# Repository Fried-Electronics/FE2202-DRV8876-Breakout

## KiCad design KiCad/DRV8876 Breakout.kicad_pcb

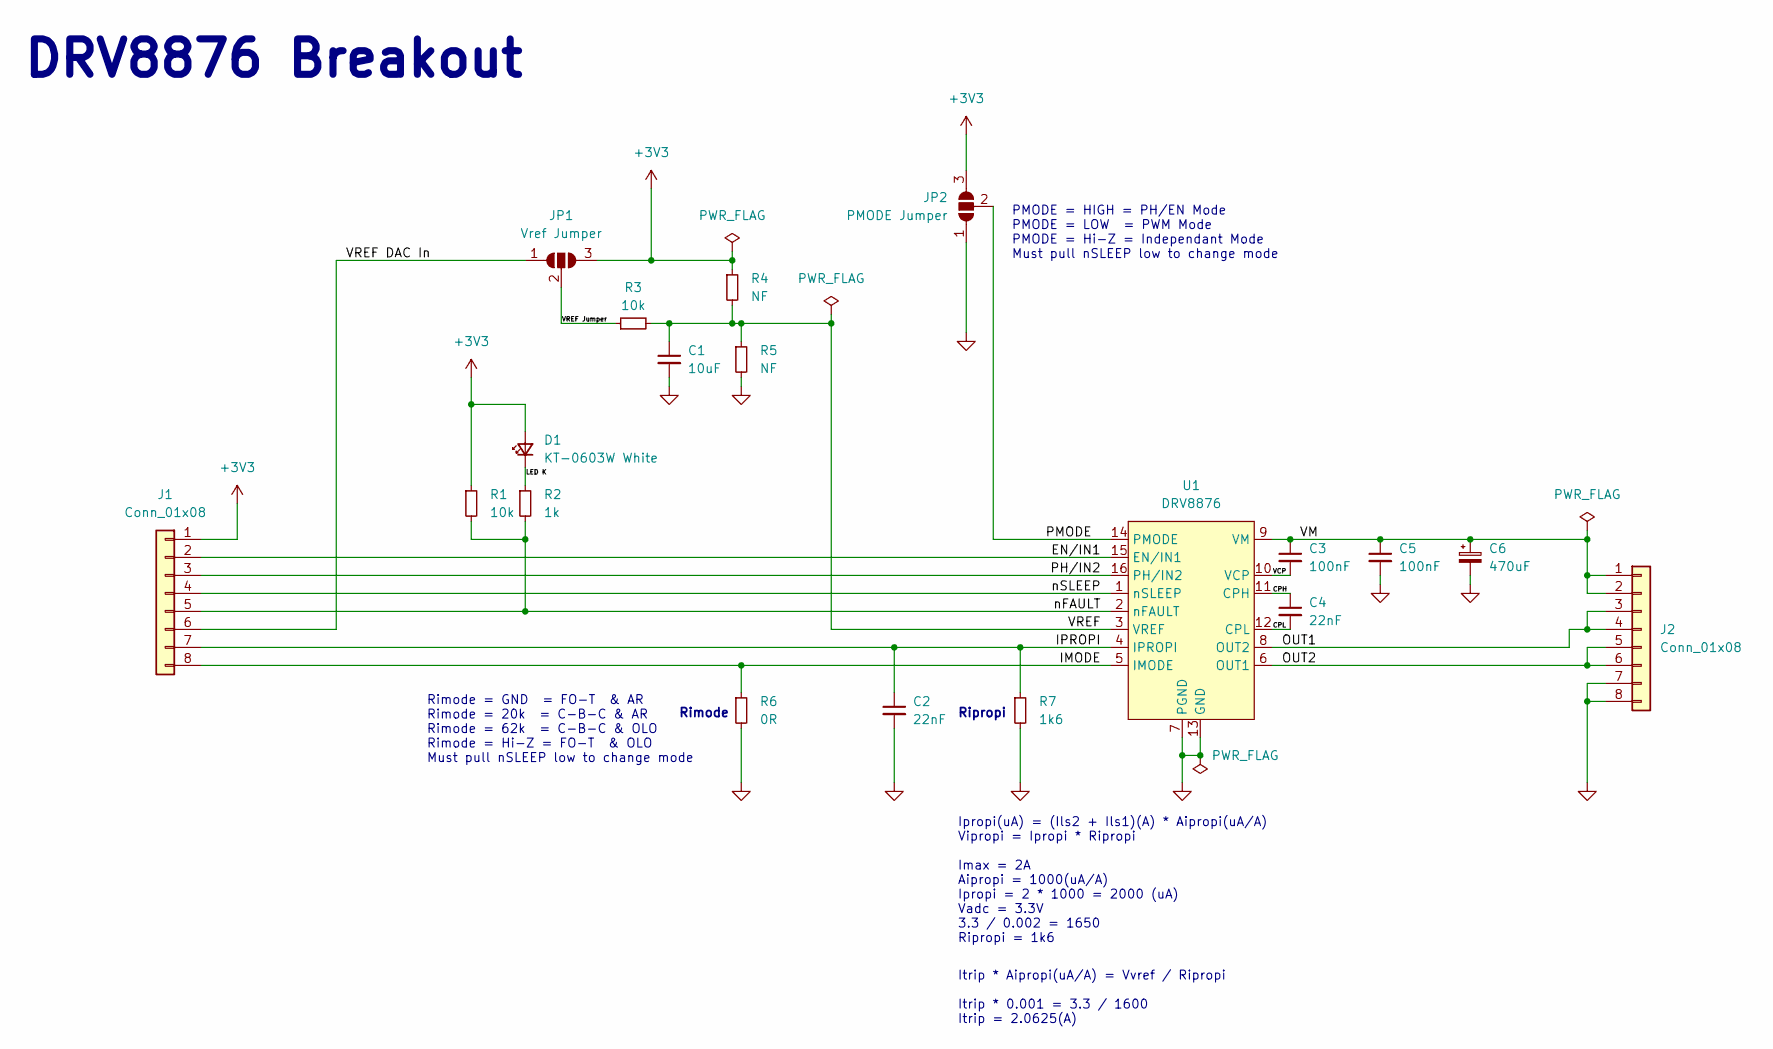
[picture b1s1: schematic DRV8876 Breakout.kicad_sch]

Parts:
C1: 10uF; C_0603_1608Metric
C2, C4: 22nF; C_0603_1608Metric
C3, C5: 100nF; C_0603_1608Metric
C6: 470uF; CP_Elec_10x10.5
D1: KT-0603W White; LED_0603_1608Metric
J1, J2: Conn_01x08; PinHeader_1x08_P2.54mm_Vertical
JP1: Vref Jumper; SolderJumper-3_P2.0mm_Open_TrianglePad1.0x1.5mm_NumberLabels
JP2: PMODE Jumper; SolderJumper-3_P2.0mm_Open_TrianglePad1.0x1.5mm_NumberLabels
R1, R3: 10k; R_0603_1608Metric
R2: 1k; R_0603_1608Metric
R4, R5: NF; R_0603_1608Metric
R6: 0R; R_0603_1608Metric
R7: 1k6; R_0603_1608Metric
U1: DRV8876; VQFN16 DRV8876

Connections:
+3V3: D1.2 (A), J1.1, JP1.3 (B), JP2.3 (B), R1.1, R4.1
/CPH: C4.1, U1.11 (CPH)
/CPL: C4.2, U1.12 (CPL)
/EN/IN1: J1.2, U1.15 (EN/IN1)
/IMODE: J1.8, R6.1, U1.5 (IMODE)
/IPROPI: C2.1, J1.7, R7.1, U1.4 (IPROPI)
/LED K: D1.1 (K), R2.1
/OUT1: J2.3, J2.4, U1.8 (OUT2)
/OUT2: J2.5, J2.6, U1.6 (OUT1)
/PH/IN2: J1.3, U1.16 (PH/IN2)
/PMODE: JP2.2 (C), U1.14 (PMODE)
/VCP: C3.2, U1.10 (VCP)
/VM: C3.1, C5.1, C6.1, J2.1, J2.2, U1.9 (VM)
/VREF: C1.1, R3.2, R4.2, R5.1, U1.3 (VREF)
/VREF DAC In: J1.6, JP1.1 (A)
/VREF Jumper: JP1.2 (C), R3.1
/nFAULT: J1.5, R1.2, R2.2, U1.2 (nFAULT)
/nSLEEP: J1.4, U1.1 (nSLEEP)
GND: C1.2, C2.2, C5.2, C6.2, J2.7, J2.8, JP2.1 (A), R5.2, R6.2, R7.2, U1.7 (PGND), U1.13 (GND)

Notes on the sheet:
Ipropi(uA) = (Ils2 + Ils1)(A) * Aipropi(uA/A) Vipropi = Ipropi * Ripropi Imax = 2A Aipropi = 1000(uA/A) Ipropi = 2 * 1000 = 2000 (uA) Vadc = 3.3V 3.3 / 0.002 = 1650 Ripropi = 1k6
Rimode = GND = FO-T & AR Rimode = 20k = C-B-C & AR Rimode = 62k = C-B-C & OLO Rimode = Hi-Z = FO-T & OLO Must pull nSLEEP low to change mode
Rimode
PMODE = HIGH = PH/EN Mode PMODE = LOW = PWM Mode PMODE = Hi-Z = Independant Mode Must pull nSLEEP low to change mode
Itrip * Aipropi(uA/A) = Vvref / Ripropi Itrip * 0.001 = 3.3 / 1600 Itrip = 2.0625(A)
Ripropi
DRV8876 Breakout

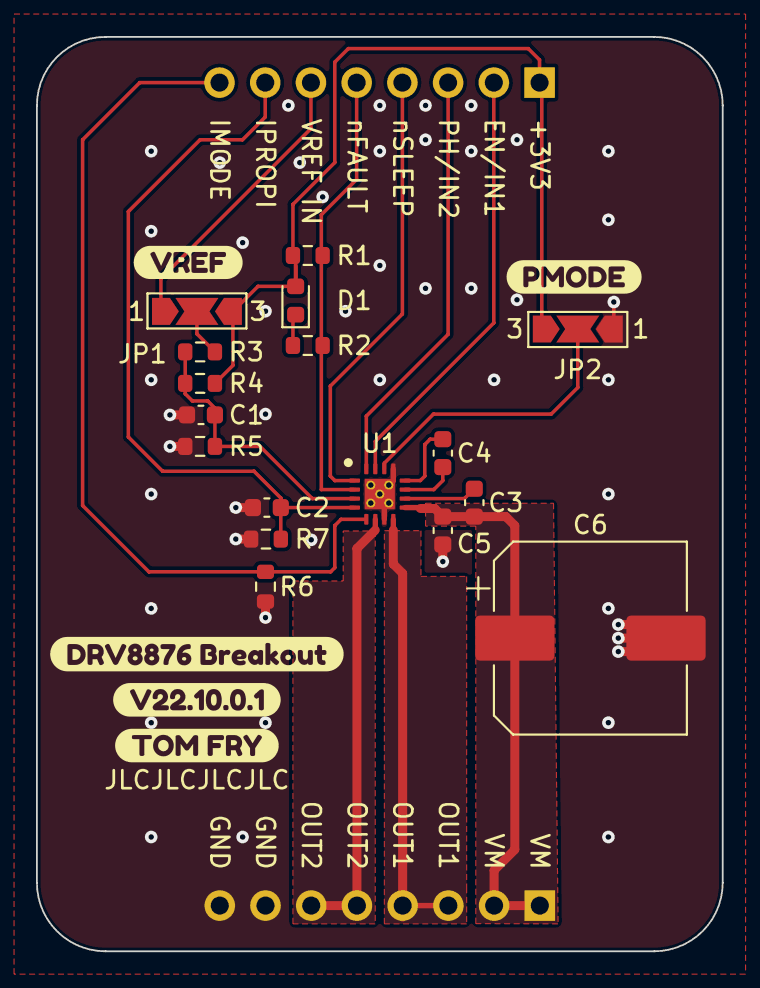
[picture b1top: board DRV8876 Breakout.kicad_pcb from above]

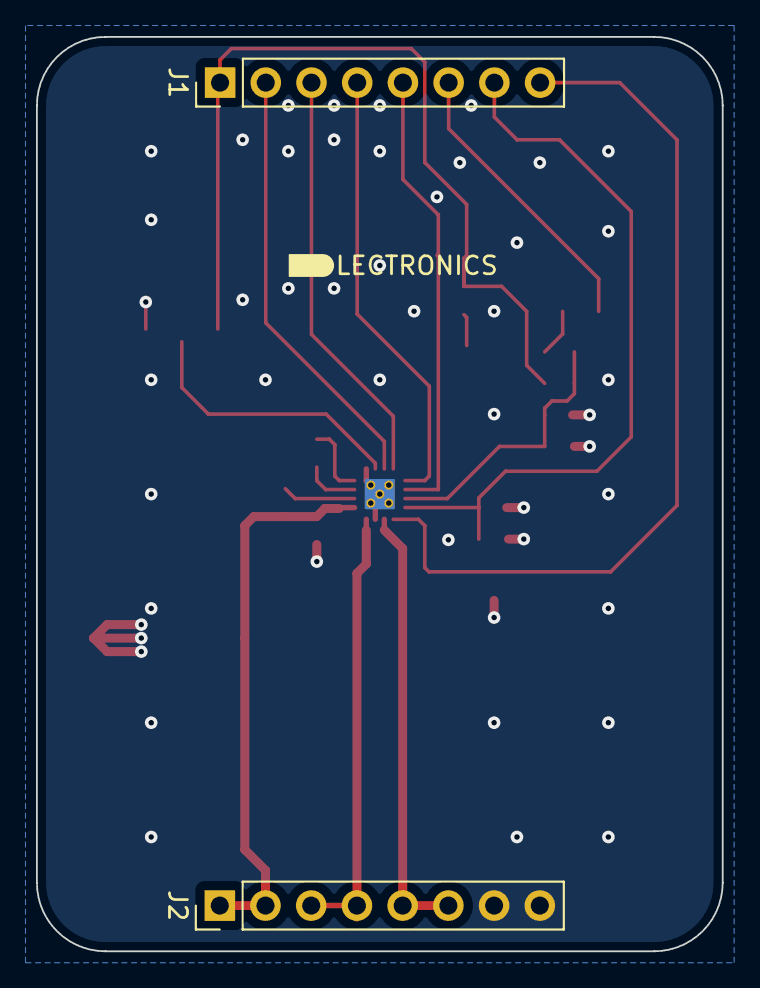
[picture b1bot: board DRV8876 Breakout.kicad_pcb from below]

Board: 2 copper layers, 38.1 x 50.8 mm, 24 parts (2 on the bottom side), 19 nets.

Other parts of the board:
kibuzzard-633DB2C4: G***; kibuzzard-633DB2C4
kibuzzard-633DB2E1: G***; kibuzzard-633DB2E1
kibuzzard-633DB48A: G***; kibuzzard-633DB48A
kibuzzard-633DB49D: G***; kibuzzard-633DB49D
kibuzzard-633DB301: G***; kibuzzard-633DB301

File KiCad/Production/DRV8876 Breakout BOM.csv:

"Source:","C:\Users\tomfr\Documents\GitHub\DRV8876-Breakout\KiCad\DRV8876 Breakout.kicad_sch"
"Date:","06/10/2022 08:51:51"
"Tool:","Eeschema (6.0.5)"
"Generator:","C:\Program Files\KiCad\6.0\bin\scripting\plugins/bom_csv_grouped_by_value.py"
"Component Count:","19"

"Individual Components:"

"Item","Qty","Reference(s)","Value","LibPart","Footprint","Datasheet"
"","","C1","10uF","Device:C_Small","Capacitor_SMD:C_0603_1608Metric","~"
"","","C2","22nF","Device:C_Small","Capacitor_SMD:C_0603_1608Metric","~"
"","","C3","100nF","Device:C_Small","Capacitor_SMD:C_0603_1608Metric","~"
"","","C4","22nF","Device:C_Small","Capacitor_SMD:C_0603_1608Metric","~"
"","","C5","100nF","Device:C_Small","Capacitor_SMD:C_0603_1608Metric","~"
"","","C6","470uF","Device:C_Polarized_Small","Capacitor_SMD:CP_Elec_10x10.5","https://www.mouser.co.uk/datasheet/2/212/KEM_A4001_EDK-1094671.pdf"
"","","D1","KT-0603W White","Device:LED_Small","LED_SMD:LED_0603_1608Metric","~"
"","","J1","Conn_01x08","Connector_Generic:Conn_01x08","Connector_PinHeader_2.54mm:PinHeader_1x08_P2.54mm_Vertical","~"
"","","J2","Conn_01x08","Connector_Generic:Conn_01x08","Connector_PinHeader_2.54mm:PinHeader_1x08_P2.54mm_Vertical","~"
"","","JP1","Vref Jumper","Jumper:SolderJumper_3_Open","Jumper:SolderJumper-3_P2.0mm_Open_TrianglePad1.0x1.5mm_NumberLabels","~"
"","","JP2","PMODE Jumper","Jumper:SolderJumper_3_Open","Jumper:SolderJumper-3_P2.0mm_Open_TrianglePad1.0x1.5mm_NumberLabels","~"
"","","R1","10k","Device:R_Small","Resistor_SMD:R_0603_1608Metric","~"
"","","R2","1k","Device:R_Small","Resistor_SMD:R_0603_1608Metric","~"
"","","R3","10k","Device:R_Small","Resistor_SMD:R_0603_1608Metric","~"
"","","R4","NF","Device:R_Small","Resistor_SMD:R_0603_1608Metric","~"
"","","R5","NF","Device:R_Small","Resistor_SMD:R_0603_1608Metric","~"
"","","R6","0R","Device:R_Small","Resistor_SMD:R_0603_1608Metric","~"
"","","R7","1k6","Device:R_Small","Resistor_SMD:R_0603_1608Metric","~"
"","","U1","DRV8876","DRV8876:DRV8876","DRV8876:VQFN16 DRV8876","https://www.ti.com/lit/ds/symlink/drv8876.pdf?ts=16648486840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"



"Collated Components:"

"Item","Qty","Reference(s)","Value","LibPart","Footprint","Datasheet"
"1","1","C1","10uF","Device:C_Small","Capacitor_SMD:C_0603_1608Metric","~"
"2","2","C2, C4","22nF","Device:C_Small","Capacitor_SMD:C_0603_1608Metric","~"
"3","2","C3, C5","100nF","Device:C_Small","Capacitor_SMD:C_0603_1608Metric","~"
"4","1","C6","470uF","Device:C_Polarized_Small","Capacitor_SMD:CP_Elec_10x10.5","https://www.mouser.co.uk/datasheet/2/212/KEM_A4001_EDK-1094671.pdf"
"5","1","D1","KT-0603W White","Device:LED_Small","LED_SMD:LED_0603_1608Metric","~"
"6","2","J1, J2","Conn_01x08","Connector_Generic:Conn_01x08","Connector_PinHeader_2.54mm:PinHeader_1x08_P2.54mm_Vertical","~"
"7","1","JP1","Vref Jumper","Jumper:SolderJumper_3_Open","Jumper:SolderJumper-3_P2.0mm_Open_TrianglePad1.0x1.5mm_NumberLabels","~"
"8","1","JP2","PMODE Jumper","Jumper:SolderJumper_3_Open","Jumper:SolderJumper-3_P2.0mm_Open_TrianglePad1.0x1.5mm_NumberLabels","~"
"9","2","R1, R3","10k","Device:R_Small","Resistor_SMD:R_0603_1608Metric","~"
"10","1","R2","1k","Device:R_Small","Resistor_SMD:R_0603_1608Metric","~"
"11","2","R4, R5","NF","Device:R_Small","Resistor_SMD:R_0603_1608Metric","~"
"12","1","R6","0R","Device:R_Small","Resistor_SMD:R_0603_1608Metric","~"
"13","1","R7","1k6","Device:R_Small","Resistor_SMD:R_0603_1608Metric","~"
"14","1","U1","DRV8876","DRV8876:DRV8876","DRV8876:VQFN16 DRV8876","https://www.ti.com/lit/ds/symlink/drv8876.pdf?ts=16648486840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"

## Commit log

2022-10-04 Updated Kicad files
2022-10-05 Finished Schematic and PCB
2022-10-05 Finished and Plotted
2022-11-04 Created STM32 Software Folder
2022-11-04 Updated DRV Code
2022-11-04 Update DRV Code
2023-04-10 Added G4 nucleo project
2023-04-10 Updated PMODE on schematic as was wrong
